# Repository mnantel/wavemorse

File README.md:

# WaveMorse

Turn a **Waveshare ESP32-S3-LCD-1.47B** (USB-C board with the 1.47" screen)
into a USB morse key for the **Morse-It** iOS app: plug an iambic paddle
(or straight key) into the ESP32, plug the ESP32 into an iPhone, and key
away — with live decode on the built-in LCD.

- **Firmware** (`morsekey/`): iambic keyer (Curtis A/B), USB MIDI device
  the phone recognizes natively (TinyMIDI-style), on-screen decode of what
  you send, straight-key auto-detection, optional piezo sidetone.
- **Shield PCB** (`shield/`): a fab-ready snap-on board with the same
  footprint as the ESP32 board — 3.5mm jack, piezo, female headers.
  Gerbers included; see [shield/README.md](shield/README.md).

| Shield top | Shield bottom |
|---|---|
|  |  |

(The non-B USB-A variant of the board also works — change `PIN_LCD_BL` to
48 and the paddle pins to 1/2 in `morsekey/config.h`.)

Plugged into an iPhone 15, the phone powers the board and Morse-It sees it as
a MIDI input device — the same mechanism the N6ARA TinyMIDI uses.

## Parts list

Everything needed for a complete key. The shield parts are all
through-hole — no surface-mount soldering.

**Core**

| Qty | Part | Where | Note |
|-----|------|-------|------|
| 1 | Waveshare **ESP32-S3-LCD-1.47B** (USB-C variant) | Waveshare store, Amazon | the "B" board; the USB-A stick also works with pin changes (below) |
| 1 | USB-C to USB-C **data** cable | — | short and known-good; see the cable note below |
| 1 | Iambic or single-lever paddle with a 3.5 mm TRS plug, or a straight key with a TS (mono) plug | — | developed with a ZN-SL single-lever paddle |

**Shield** (optional, but makes the key a tidy snap-together unit — see
[shield/README.md](shield/README.md) for ordering the PCB and assembly)

| Qty | Part | DigiKey P/N | Note |
|-----|------|-------------|------|
| 1 | Shield PCB (`shield/morsekey-shield-gerbers.zip`) | JLCPCB, PCBWay, OSH Park… | 2 layers, 1.6 mm, all fab defaults |
| 1 | Same Sky SJ1-3523N 3.5 mm TRS jack | **CP1-3523N-ND** | through-hole, right angle |
| 1 | Same Sky CPT-1207-5LTH-T piezo transducer | **2223-CPT-1207-5LTH-T-ND** | optional sidetone; ø12.5 mm, 5.0 mm pitch |
| 2 | 1×9 female header socket, 2.54 mm (Sullins PPTC091LFBN-RC) | **S7007-ND** | on the shield |
| 2 | 1×9 male pin header, 2.54 mm, breakaway | **S1012EC-09-ND** | soldered to the ESP32 board, pins down |
| 2 | M2 screw + standoff | — | optional, for case mounting |

Piezo alternates on the same footprint: TDK **PS1240P02BT**
(445-2525-1-ND) or Same Sky **CPT-1206-3TH-T** (2223-CPT-1206-3TH-T-ND).
Any ~12 mm two-pin piezo *transducer* (externally driven, not a
self-oscillating "indicator"/active buzzer) with ~5 mm pin spacing fits —
the shield's piezo holes are slots that take about 4–6 mm.
A passive transducer has no electrical polarity — if it has a "+" mark or
longer lead, put that in the square pad (GPIO5) by convention.

No resistors or capacitors are needed: the paddle inputs use the ESP32's
internal pull-ups, and the piezo is driven directly by PWM.

**About the cable:** a worn or charge-grade cable can carry enough data
to enumerate (the device name shows up) but not to flash or run MIDI —
symptoms are `No serial data received` on upload, or the board appearing
without a serial port. If anything USB acts strange, swap the cable first.

## Wiring the paddle

The paddle connects to the board's edge header. With a 3.5mm TRS jack
(standard paddle wiring):

| Paddle / jack        | Board header pin |
|----------------------|------------------|
| Tip (left paddle)    | **GPIO2** (dit)  |
| Ring (right paddle)  | **GPIO3** (dah)  |
| Sleeve (common)      | **GND**          |

All three are on the edge header (follow the silkscreen labels GND, 2, 3).
The inputs use internal pull-ups; the paddle just shorts them to ground — no
resistors needed. If dit/dah feel reversed, flip "Paddle: Swapped" in the
settings menu (or swap the wires). Free header GPIOs on this board are
2–11; avoid 1 (battery ADC) and 12/13 (IMU interrupts).

## Connecting to the iPhone

A plain **USB-C to USB-C cable** — the phone powers the board (~100 mA,
well within what the port supplies). The board enumerates as a MIDI device
named **MorseKey**.

## Morse-It setup

Two ways to use it — pick one in the settings menu ("MIDI" item):

**PADDLE mode (default, recommended).** The board sends the raw paddle
contacts as two MIDI notes (dit = note 18, dah = note 38, channel 1 —
Morse-It's documented defaults) and Morse-It runs
its own iambic keyer, sidetone and speed:
1. In Morse-It, set the key type to **Iambic Paddle**, matching the A/B
   mode shown on the board (default: A).
2. In the settings, under the hardware/MIDI interface section, select the
   **MorseKey** MIDI device and assign the two notes to the dit and dah
   areas (use the app's "learn" function: tap the field, press a paddle).
3. Set Morse-It's keyer speed to match the WPM shown on the board's screen
   so the on-screen decode matches what the app hears.

**KEYER mode.** The board does the iambic keying itself and sends the result
as a single on/off note (note 18) — configure Morse-It as a **Straight Key**.
What Morse-It receives is then exactly what the board's screen shows, and
speed is controlled on the board.

## Controls

**BOOT quick press** opens the on-screen settings menu; **BOOT held ~1 s**
(outside the menu) toggles iambic A/B directly — the status bar reflects it
immediately. In the menu, navigate with the paddle:

| Input in menu     | Effect                                   |
|-------------------|------------------------------------------|
| Dit paddle        | Next item                                |
| Dah paddle / BOOT tap | Change the selected value            |
| BOOT held ~1 s    | Save and exit                            |

Settings: speed (10–30 WPM), iambic A/B, MIDI mode (Paddle/Keyer), paddle
swap, sidetone on/off. All persist across power cycles. With a straight
key plugged in, navigate with the key and change values with BOOT taps.

The screen shows a centered status bar (WPM, iambic mode, MIDI mode, USB
state), the in-progress dit/dah pattern in yellow, and three lines of
decoded text: finished words in white, the word being keyed in cyan, and a
blinking cursor marking where the next character lands. The RGB LED is red while keying, dim
cyan at idle in PADDLE mode, dim green in KEYER mode. Unrecognized patterns
decode as `#`.

## Building and flashing

With [arduino-cli](https://arduino.github.io/arduino-cli/):

```sh
arduino-cli config add board_manager.additional_urls \
  https://espressif.github.io/arduino-esp32/package_esp32_index.json
arduino-cli core update-index
arduino-cli core install esp32:esp32
arduino-cli lib install "GFX Library for Arduino"
./flash.sh
```

Or in the Arduino IDE, open `morsekey/morsekey.ino` with these Tools
settings: board **ESP32S3 Dev Module**, USB Mode **USB-OTG (TinyUSB)**
(required for MIDI), USB CDC On Boot **Enabled**, Flash Size **16MB**,
PSRAM **OPI PSRAM**. Install the "GFX Library for Arduino" library.
(IDE builds enumerate with the generic name "ESP32S3_DEV" — the "MorseKey"
device name comes from a `-DUSB_PRODUCT` flag that `flash.sh` sets; either
name works fine in Morse-It.)

A brand-new board's factory firmware ignores the automatic reset, so the
first flash needs the bootloader forced: unplug, hold **BOOT**, plug back
in, release BOOT after a second or two (the screen stays dark), then run
`./flash.sh`. After a forced flash, unplug/replug once to start the
firmware. From then on `./flash.sh` resets the board itself; if an upload
occasionally fails with `No serial data received`, just run it again. With
several USB serial devices attached, pass the port explicitly:
`./flash.sh /dev/cu.usbmodemXXXX`.

## Configuration

Runtime settings live in the on-screen menu. Compile-time options in
`morsekey/config.h`: paddle/piezo pins, MIDI note numbers, sidetone pitch,
defaults, and the paddle debounce time.

**Debounce:** a contact change is accepted only after the line has been
free of edges for `PADDLE_DEBOUNCE_MS` (6 ms). Edges are timestamped by
interrupt, so even sub-millisecond bounce is seen. 6 ms was measured on a
ZN-SL: press bounce lasts up to ~12 ms with quiet gaps under 4 ms inside
it, and switching one contact induces brief glitches on the other line.
A noisier paddle may need a little more; much more starts to add audible
latency.

## Shield PCB

`shield/` contains a manufacturable snap-on shield (KiCad design, Gerbers,
1:1 placement PDF) with the same footprint as the board: one 3.5mm jack
that takes either a paddle (TRS) or a straight key (TS mono — auto-detected,
status bar shows `SKEY`), plus an optional piezo sidetone on GPIO5. See
`shield/README.md` for ordering and assembly.

## Possible extensions

- **BLE MIDI**: the ESP32-S3 has Bluetooth; Morse-It also accepts BLE MIDI,
  which would make the key wireless (the board has a LiPo charger and BAT
  connector).
- **IMU gestures**: the onboard QMI8658 accelerometer could open the menu
  on a double-tap.

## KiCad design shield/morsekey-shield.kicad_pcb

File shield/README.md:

# MorseKey shield (v2)

A snap-on shield for the Waveshare ESP32-S3-LCD-1.47B with the **same
footprint as the board itself (36.37 × 20.32 mm)**: one 3.5mm jack that
serves both an iambic paddle (TRS plug) and a straight key (TS mono plug —
the firmware auto-detects it), an optional piezo sidetone, and female
headers the ESP32 board (male pins soldered pointing down) plugs into.

The jack opens at the antenna end, its bushing protruding past the edge the
same way the USB-C does at the other end. Renders: `render-top.png` /
`render-bottom.png`.

## Ordering (JLCPCB, PCBWay, OSH Park…)

Upload `morsekey-shield-gerbers.zip` to the fab's quote page. All defaults
are fine: 2 layers, 1.6 mm FR-4, HASL, any color, smallest quantity
(usually 5). Cost is a few dollars plus shipping.

**Before ordering — the paper test:** print `placement-1to1.pdf` at 100%
scale (no "fit to page"), hold the ESP32 board's header holes over the
drawing, and confirm every hole lines up. This catches any dimension error
while it's still free.

## Bill of materials

| Qty | Part | DigiKey P/N | Note |
|-----|------|-------------|------|
| 1 | Same Sky SJ1-3523N 3.5 mm TRS jack | **CP1-3523N-ND** | through-hole, right angle |
| 1 | Same Sky CPT-1207-5LTH-T piezo transducer | **2223-CPT-1207-5LTH-T-ND** | optional — sidetone; ø12.5 mm, 5.0 mm pin pitch, 85 dB |
| 2 | 1×9 female header socket, 2.54 mm | e.g. **S7007-ND** (Sullins PPTC091LFBN-RC) | standard 8.5 mm height |
| 2 | 1×9 male pin header, 2.54 mm | e.g. **S1012EC-09-ND** (breakaway) | solder to the ESP32 board, pins down |
| 2 | M2 screw + standoff | — | optional — case mounting, USB end corners |

Piezo alternates (same footprint): TDK **PS1240P02BT**
(DigiKey 445-2525-1-ND, often backordered) or Same Sky **CPT-1206-3TH-T**
(2223-CPT-1206-3TH-T-ND). Any ~12 mm two-pin piezo *transducer*
(externally driven — not an "indicator") with ~5 mm pin spacing fits:
the piezo pads are plated slots, so pin spacing anywhere from about 4 to
6 mm drops in (datasheet pitch is 5.0 ±0.5 mm, and the original round
holes at exactly 5.0 mm were too tight for real parts).

## Connections (all done by the PCB)

| Net | Header pin | Goes to |
|-----|-----------|---------|
| DIT | GPIO2 | jack tip |
| DAH | GPIO3 | jack ring |
| PIEZO | GPIO5 | piezo + |
| GND | both G pins | jack sleeve, piezo −, ground pour |

**Paddle vs straight key:** a TRS (stereo) plug = paddle on tip/ring. A TS
(mono) straight-key plug grounds the ring permanently; the firmware detects
this (at power-up, or after 8 s of continuous "dah") and turns the tip into
a straight-key input — the status bar shows `SKEY`. Unplug it and paddle
mode returns automatically.

## Assembly

1. Solder the male pin headers to the ESP32 board pointing **down** (away
   from the screen).
2. Solder female sockets, the jack, and optionally the piezo to the shield
   top. The "USB" silk label marks the USB-C end. The jack only fits one
   way; the sockets are symmetric. The piezo transducer is unpolarized —
   if it has a "+" mark or longer lead, put it in the square pad (GPIO5)
   by convention.
3. Snap the ESP32 board in, screen up, USB-C over the "USB" label.

## Regenerating

`generate_shield.py` builds the .kicad_pcb from scratch (see its header for
the KiCad python invocation), then:

```sh
kicad-cli pcb drc --refill-zones --save-board --severity-error --exit-code-violations -o drc.rpt morsekey-shield.kicad_pcb
kicad-cli pcb export gerbers --check-zones -l "F.Cu,B.Cu,F.Paste,B.Paste,F.Silkscreen,B.Silkscreen,F.Mask,B.Mask,Edge.Cuts" -o gerbers/ morsekey-shield.kicad_pcb
kicad-cli pcb export drill --format excellon --excellon-separate-th -o gerbers/ morsekey-shield.kicad_pcb
```

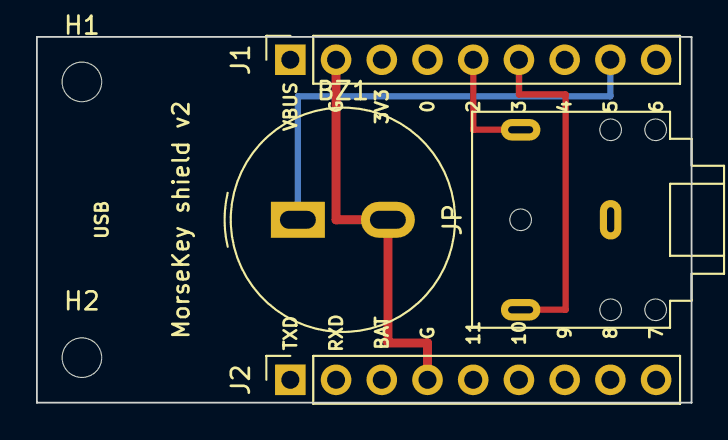
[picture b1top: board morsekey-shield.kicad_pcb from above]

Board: 2 copper layers, 36.4 x 20.3 mm, 6 parts (0 on the bottom side), 4 nets.

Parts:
BZ1: Buzzer_TDK_PS1240P02BT_D12.2mm_H6.5mm
H1, H2: MountingHole_2.2mm_M2
J1, J2: PinSocket_1x09_P2.54mm_Vertical
JP: Jack_3.5mm_CUI_SJ1-3523N_Horizontal

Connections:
DAH: J1.6, JP.R
DIT: J1.5, JP.T
GND: BZ1.2, J1.2, J2.4, JP.S
PIEZO: BZ1.1, J1.8

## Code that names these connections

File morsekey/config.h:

#pragma once

// ---------------------------------------------------------------------------
// MorseKey configuration — Waveshare ESP32-S3-LCD-1.47
// ---------------------------------------------------------------------------

// Paddle inputs (edge header, active LOW, internal pull-ups).
// Wire a 3.5mm TRS jack: tip -> DIT, ring -> DAH, sleeve -> GND.
// Note: on the 1.47B variant GPIO1 is the battery ADC and GPIO12/13 are IMU
// interrupts; GPIO2-GPIO11 are the free header pins.
#define PIN_DIT 2
#define PIN_DAH 3

// Piezo sidetone pin. The MorseKey shield has a piezo footprint wired to
// GPIO5; harmless if unpopulated. Enable/disable at runtime in the menu.
#define PIN_SIDETONE 5
#define SIDETONE_HZ 600

// Onboard peripherals (fixed by the board, do not change).
#define PIN_LCD_MOSI 45
#define PIN_LCD_SCK 40
#define PIN_LCD_CS 42
#define PIN_LCD_DC 41
#define PIN_LCD_RST 39
// Backlight is GPIO46 on the USB-C ESP32-S3-LCD-1.47B (this board).
// On the USB-A ESP32-S3-LCD-1.47 it is GPIO48 instead.
#define PIN_LCD_BL 46
#define PIN_BOOT_BTN 0
#define PIN_RGB_LED 38

// MIDI notes sent to Morse-It. These match Morse-It's documented adapter
// defaults (https://pacolabs.com/iOS/MorseIt/MIDI/): dit = 18, dah = 38,
// straight key = 18, channel 0 - so the app needs little or no note
// assignment. Reassignable in the app if you change them here.
#define MIDI_CH 0
#define NOTE_DIT 18 // paddle mode: dit contact
#define NOTE_DAH 38 // paddle mode: dah contact
#define NOTE_KEY 18 // keyer mode / straight key: locally keyed output

// Defaults (changeable at runtime in the settings menu, saved to flash).
#define DEFAULT_WPM 20
#define DEFAULT_IAMBIC_B false   // false = mode A
#define DEFAULT_MIDI_PADDLE true // true = send raw paddle, false = send keyed output
#define DEFAULT_SWAP false       // swap dit/dah paddles
#define DEFAULT_TONE true        // piezo sidetone

// Debounce time for paddle contacts, in ms: a contact change is accepted
// once the line has been edge-free this long. Measured on a ZN-SL: press
// bounce lasts up to 12ms with quiet gaps under 4ms inside it.
#define PADDLE_DEBOUNCE_MS 6
